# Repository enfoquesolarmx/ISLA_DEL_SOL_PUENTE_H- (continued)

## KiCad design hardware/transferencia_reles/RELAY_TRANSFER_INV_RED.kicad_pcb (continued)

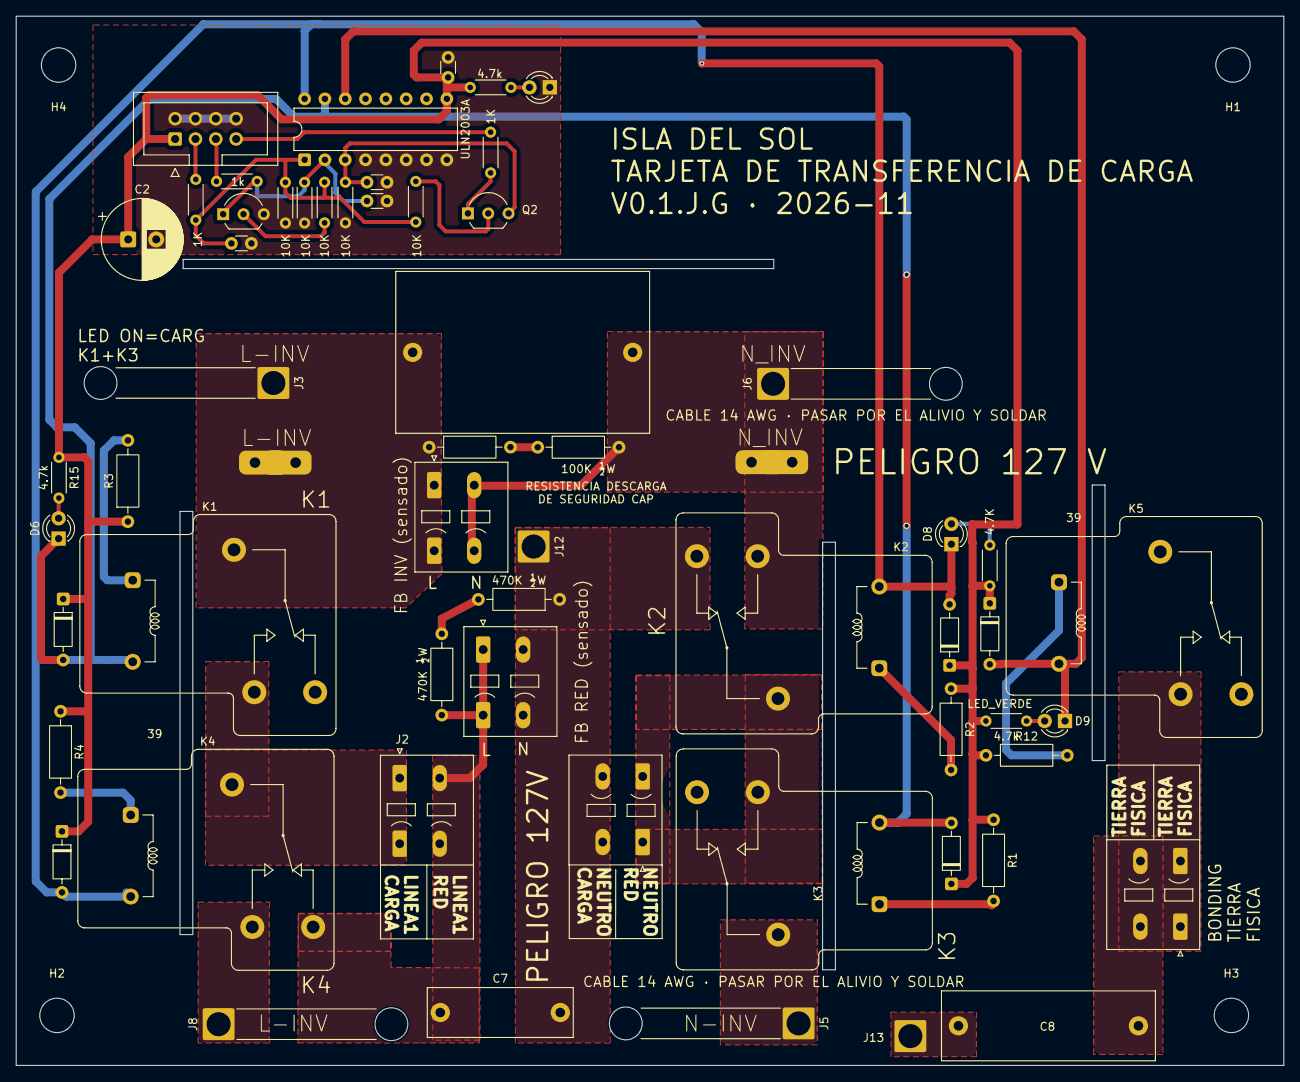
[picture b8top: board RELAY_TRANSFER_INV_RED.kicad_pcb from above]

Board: 2 copper layers, 158.4 x 131.1 mm, 64 parts (0 on the bottom side), 32 nets.
